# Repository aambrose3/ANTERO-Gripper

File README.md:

ANTERO-Gripper
MATLAB code for modeling, optimizing, and experimentally evaluating the ANTERO gripper and its 5-bar, 3-DOF (5B3D) finger mechanism.
This repository brings together:
a static finger model for contact-force estimation,
finger geometry and compliance optimization studies,
beam spring optimization scripts,
force-control analysis utilities, and
grasp-force validation scripts based on experimental data.
Repository structure
`5B3D-Finger-Model`
Baseline 5B3D finger static model and contact-force estimation code.
Key files:
`Main.m` — runs the main static-model sweep and saves results into the `Results/` directory.
`contactSolver.m`, `fastContactSolver.m`, `getJacobians.m`, `getParam.m`, `getSpring.m`, `updateParam.m` — supporting model functions.
`Results/` — generated outputs and follow-on plotting/analysis scripts.
`5B3D-Finger-Optimization`
Finger design-space exploration and optimization utilities.
Key files:
`Main.m` — runs a model sweep over finger states.
`Optimization.m` — performs design optimization over parameters such as link length and compliance-related terms.
`OptimizationAnalysis.m` — post-processes optimization outputs.
`FingerLinkOptimization.m` — helper script for optimization studies.
`Results/` — saved outputs and visualizations.
`5B3D-Spring-Optimization`
Beam spring modeling and stiffness optimization.
Key files:
`OptimizeSpringStiffness.m` — main entry point for spring optimization.
`solveBVP.m`, `bcfcn.m`, `initFcn.m` — boundary-value-problem setup.
`plotSpring.m`, `plotStress.m`, `plotStiffness.m`, `plotThickness.m` — visualization utilities.
`OptimalSpring.mat`, `OptimalSpring_Plus.mat` — saved optimization outputs.
`Force-Control-Testing`
Utilities for unpacking experimental datasets and analyzing force-control / frequency-response behavior.
Key files:
`unpackTeensy.m`
`unpackRokubi.m`
`interpData.m`
`FrequencyResponseAnalysis.m`
`Grasp-Force-Testing`
Scripts for comparing modeled grasp force against measured force-torque data.
Key files:
`Data/unpackTeensyData.m`
`Data/unpackRokubiData.m`
`interpData.m`
`GraspForceTestingAnalysis.m`
plotting utilities and exported figures
`ANTERO-Mid-Level-Control`
Placeholder folder for mid-level control content.
Requirements
This repository is written in MATLAB.
Depending on the scripts you run, you may need MATLAB functionality for:
symbolic math,
parallel computing, and
constrained optimization.
Several scripts also expect local experimental datasets to be available as `.csv`, `.log`, or `.mat` files in specific folder layouts.
Quick start
1. Clone the repository
```bash
git clone https://github.com/aambrose3/ANTERO-Gripper.git
cd ANTERO-Gripper
```
2. Open the repo in MATLAB
Open MATLAB and set the current folder to the repository root, or add the relevant subfolder to your MATLAB path.
3. Run the model or analysis you need
Static 5B3D finger model
```matlab
cd('5B3D-Finger-Model')
run('Main.m')
```
Finger optimization studies
```matlab
cd('5B3D-Finger-Optimization')
run('Main.m')              % model sweep
run('Optimization.m')      % design optimization
```
Spring optimization
```matlab
cd('5B3D-Spring-Optimization')
run('OptimizeSpringStiffness.m')
```
Grasp-force validation workflow
From `Grasp-Force-Testing`, run the scripts in this order:
```matlab
run('Data/unpackTeensyData.m')
run('Data/unpackRokubiData.m')
run('interpData.m')
run('GraspForceTestingAnalysis.m')
```
Expected workflow
5B3D model and optimization
Use the `5B3D-Finger-Model` and `5B3D-Finger-Optimization` folders when you want to:
sweep the finger through joint configurations,
estimate proximal/distal contact forces,
study feasible workspaces,
evaluate mechanical advantage, or
optimize design variables.
Spring design
Use `5B3D-Spring-Optimization` to generate and evaluate compliant spring designs and saved spring models.
Experimental validation
Use `Force-Control-Testing` and `Grasp-Force-Testing` to:
unpack Teensy and Rokubi datasets,
synchronize or interpolate time series,
analyze frequency response, and
compare modeled versus measured grasp force.
Important notes
Hard-coded paths and filenames
Many scripts use hard-coded relative paths and dataset names. Before running them, you will likely need to update file paths for your local machine and dataset organization.
Examples include paths such as:
`60x75\5_HZ\T1.csv`
`60x75\5_HZ\T1-FT.csv`
`Grasp_Force_Testing_Rokubi\90x90\T1.log`
`Data/Matched_Data_60x45.mat`
Results directories
Some scripts save outputs directly into `Results/` or into `.mat` files in the working directory. Running scripts from the intended folder helps avoid path issues.
Research code
This repository appears to be organized as a research codebase rather than a polished MATLAB package. Expect to inspect the top of each script for:
user settings,
sweep ranges,
optimization bounds,
dataset filenames, and
plotting/export behavior.
Suggested order for new users
If you are exploring the repo for the first time, a good path is:
Start with `5B3D-Finger-Model/Main.m` to understand the base model.
Move to `5B3D-Finger-Optimization/Optimization.m` for design studies.
Use `5B3D-Spring-Optimization/OptimizeSpringStiffness.m` for compliant spring design.
Run the experimental workflows in `Grasp-Force-Testing` and `Force-Control-Testing` once your data files are in place.
License
This project is licensed under the Apache License 2.0. See the `LICENSE` file for details.
Author
Repository author: Alexander B. Ambrose
---
If you use this code in academic work, consider citing the repository and any associated publications from the project.

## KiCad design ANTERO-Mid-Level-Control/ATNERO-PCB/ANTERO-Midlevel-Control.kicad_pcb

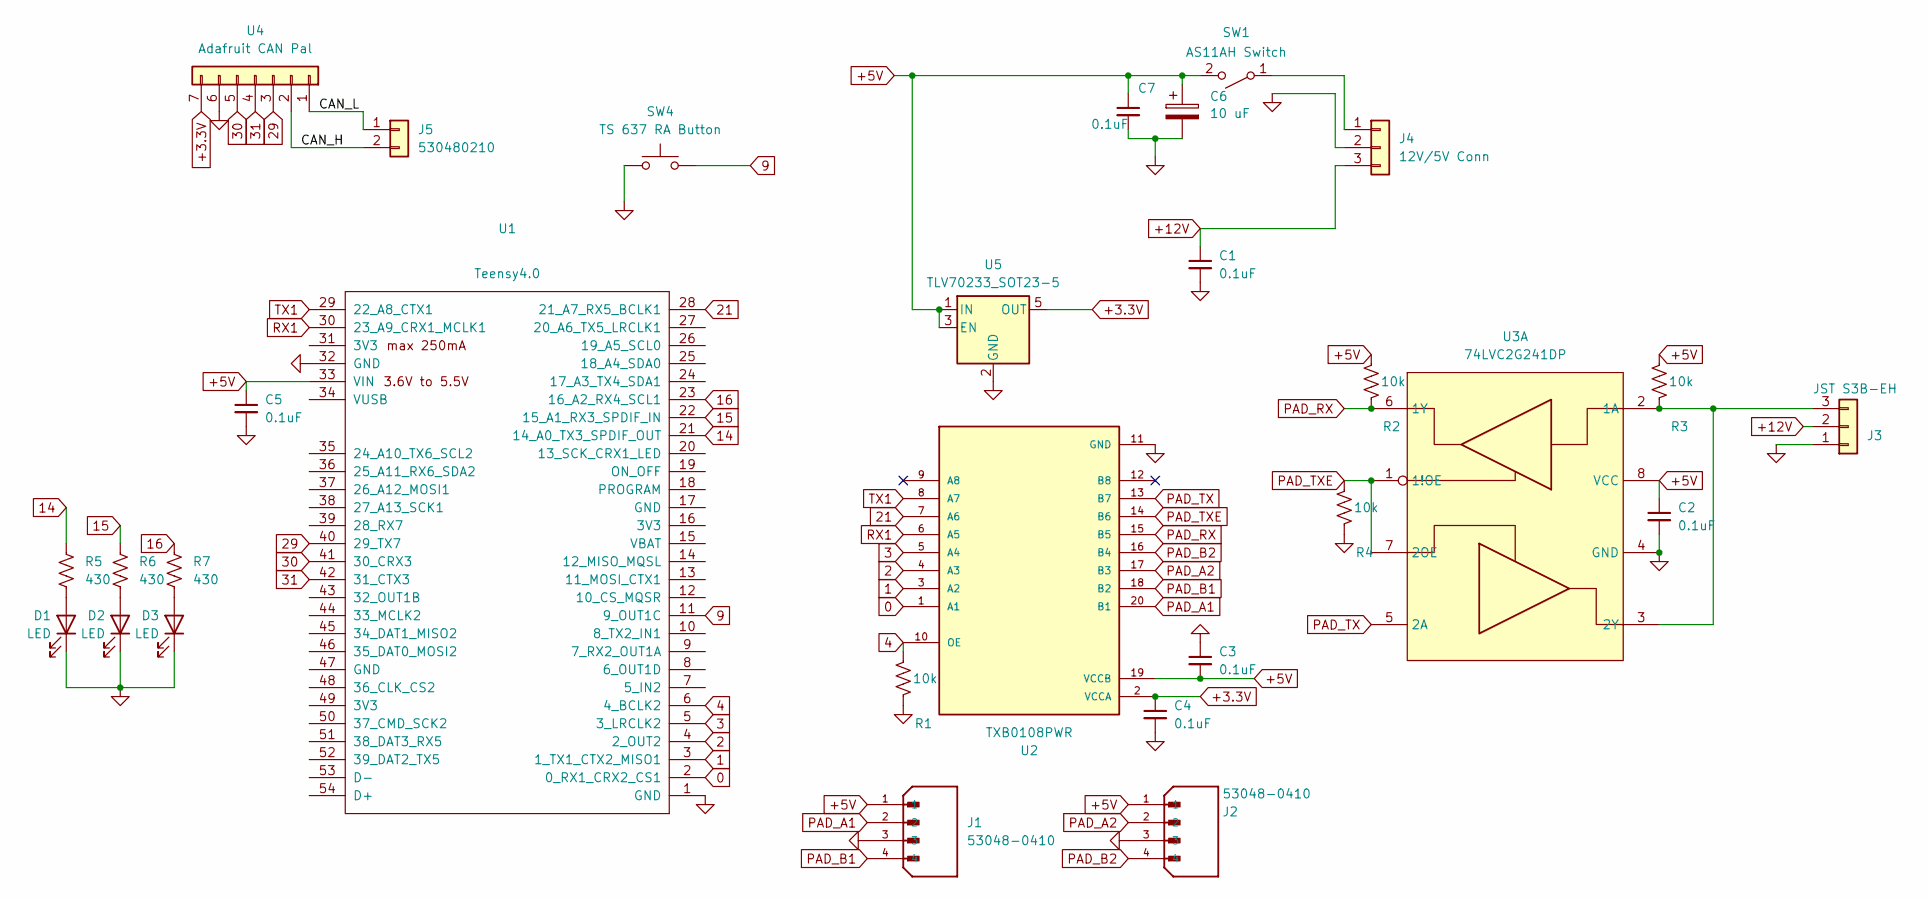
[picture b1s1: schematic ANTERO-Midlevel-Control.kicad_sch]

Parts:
C1, C2, C3, C4, C5, C7: 0.1uF; C_0805_2012Metric_Pad1.18x1.45mm_HandSolder; Digikey N/A
C6: 10 uF; CP_Elec_5x5.8
D1, D2, D3: LED; LED_0402_1005Metric_Pad0.77x0.64mm_HandSolder
J1, J2: 53048-0410; Molex_PicoBlade_53048-0410_1x04_P1.25mm_Horizontal; PARTREV A
J3: JST S3B-EH; JST_EH_S3B-EH_1x03_P2.50mm_Horizontal
J4: 12V/5V Conn; Molex_PicoBlade_53048-0310_1x03_P1.25mm_Horizontal
J5: 530480210; Molex_PicoBlade_53048-0210_1x02_P1.25mm_Horizontal
R1, R2, R3, R4: 10k; R_0805_2012Metric; Digikey N/A
R5, R6, R7: 430; R_0805_2012Metric; Digikey N/A
SW1: AS11AH Switch; AS1XAH
SW4: TS 637 RA Button; TS-637-RA
U1: Teensy4.0; Teensy40_SMT
U2: TXB0108PWR; SOP65P640X120-20N; PARTREV H
U3: 74LVC2G241DP; TSSOP-8_3x3mm_P0.65mm
U4: Adafruit CAN Pal; Adafruit Can Pal; Digikey N/A
U5: TLV70233_SOT23-5; SOT-23-5

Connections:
0: U1.2 (0_RX1_CRX2_CS1), U2.1 (A1)
1: U1.3 (1_TX1_CTX2_MISO1), U2.3 (A2)
2: U1.4 (2_OUT2), U2.4 (A3)
3: U1.5 (3_LRCLK2), U2.5 (A4)
4: R1.2, U1.6 (4_BCLK2), U2.10 (OE)
9: SW4.2, U1.11 (9_OUT1C)
14: R5.2, U1.21 (14_A0_TX3_SPDIF_OUT)
15: R6.2, U1.22 (15_A1_RX3_SPDIF_IN)
16: R7.2, U1.23 (16_A2_RX4_SCL1)
21: U1.28 (21_A7_RX5_BCLK1), U2.7 (A6)
29: U1.40 (29_TX7), U4.3 (RX)
30: U1.41 (30_CRX3), U4.5 (SLNT)
31: U1.42 (31_CTX3), U4.4 (TX)
+3.3V: C4.1, U2.2 (VCCA), U4.7 (CANL), U5.5 (OUT)
+5V: C2.1, C3.2, C5.1, C6.1, C7.1, J1.1, J2.1, R2.2, R3.2, SW1.2 (B), U1.33 (VIN), U2.19 (VCCB), U3.8 (VCC), U5.1 (IN), U5.3 (EN)
+12V: C1.1, J3.2, J4.3
/CAN_H: J5.2, U4.2 (GND)
/CAN_L: J5.1, U4.1 (Vcc)
GND: C1.2, C2.2, C3.1, C4.2, C5.2, C6.2, C7.2, D1.1 (K), D2.1 (K), D3.1 (K), J1.3, J2.3, J3.1, J4.2, R1.1, R4.1, SW4.1, U1.1 (GND), U1.32 (GND), U2.11 (GND), U3.4 (GND), U4.6 (CANH), U5.2 (GND)
unnamed: D1.2 (A), R5.1
unnamed: D2.2 (A), R6.1
unnamed: D3.2 (A), R7.1
unnamed: J3.3, R3.1, U3.2 (1A), U3.3 (2Y)
unnamed: J4.1, SW1.1 (A)
PAD_A1: J1.2, U2.20 (B1)
PAD_A2: J2.2, U2.17 (B3)
PAD_B1: J1.4, U2.18 (B2)
PAD_B2: J2.4, U2.16 (B4)
PAD_RX: R2.1, U2.15 (B5), U3.6 (1Y)
PAD_TX: U2.13 (B7), U3.5 (2A)
PAD_TXE: R4.2, U2.14 (B6), U3.1 (1!OE), U3.7 (2OE)
RX1: U1.30 (23_A9_CRX1_MCLK1), U2.6 (A5)
TX1: U1.29 (22_A8_CTX1), U2.8 (A7)

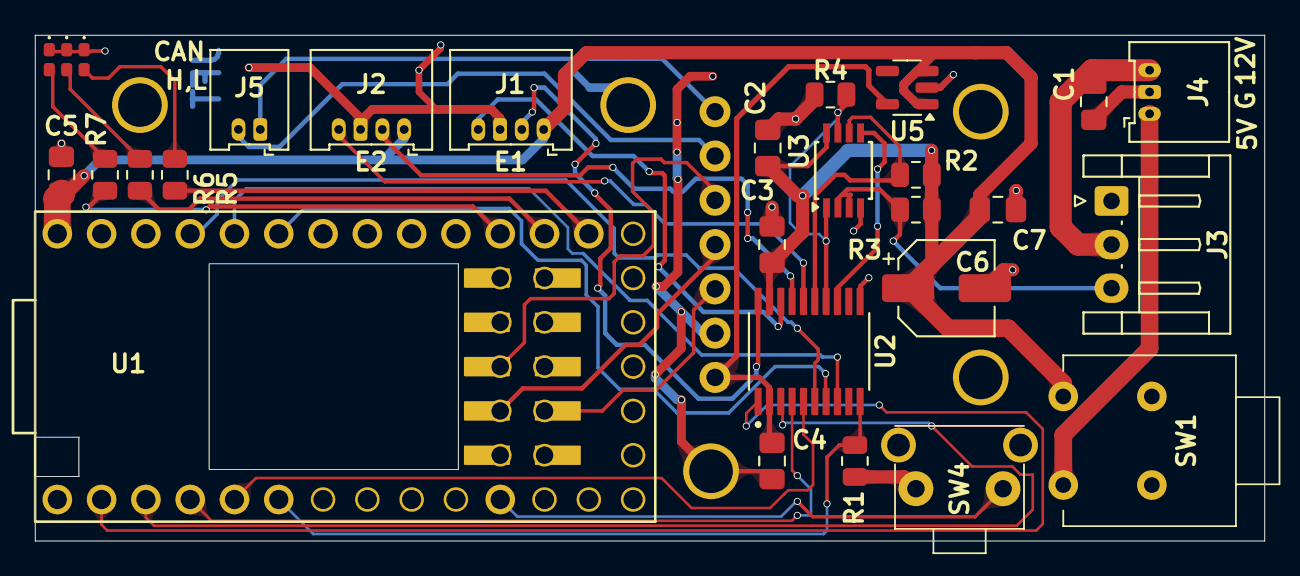
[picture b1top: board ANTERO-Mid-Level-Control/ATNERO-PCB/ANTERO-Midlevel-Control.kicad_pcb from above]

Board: 2 copper layers, 70.5 x 29.0 mm, 29 parts (1 on the bottom side), 33 nets.

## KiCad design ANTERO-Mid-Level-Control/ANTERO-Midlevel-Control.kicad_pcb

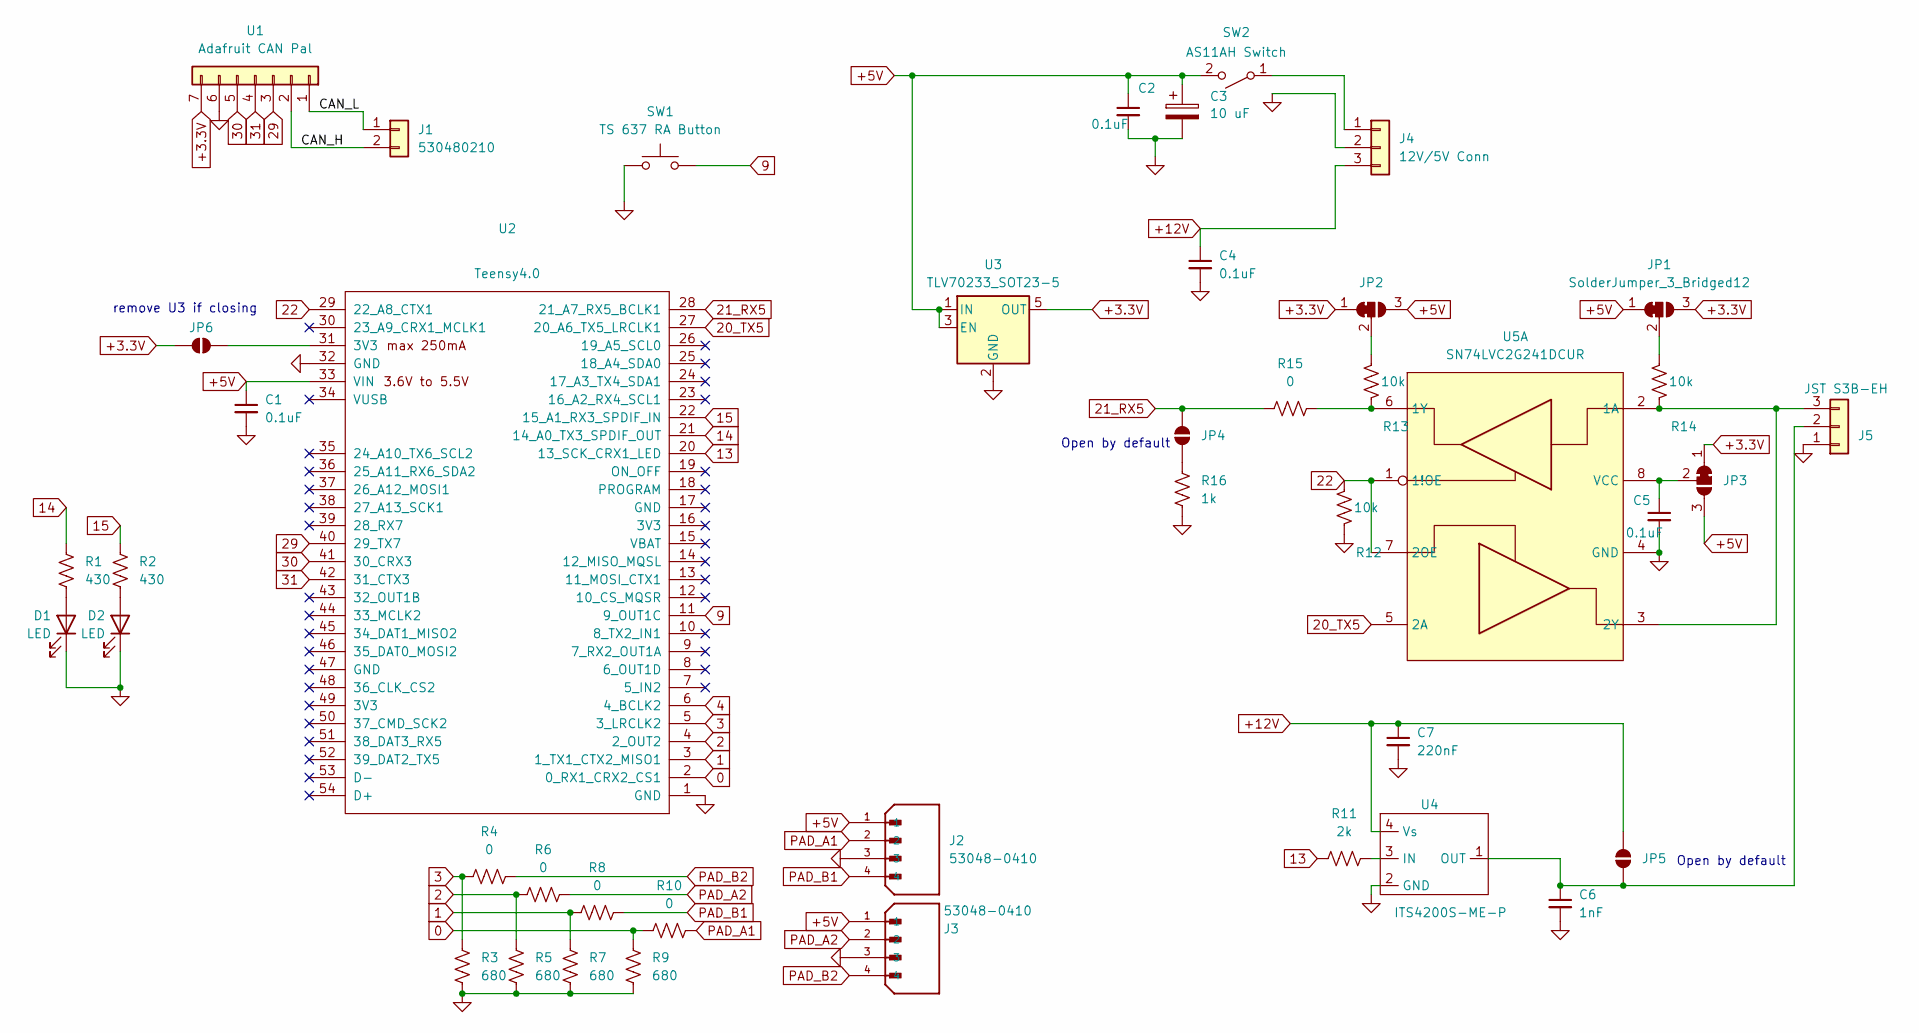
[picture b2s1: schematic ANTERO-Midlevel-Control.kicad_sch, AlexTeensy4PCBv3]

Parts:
C1, C2, C4, C5: 0.1uF; C_0805_2012Metric_Pad1.18x1.45mm_HandSolder; Digikey N/A
C3: 10 uF; CP_Elec_5x5.8
C6: 1nF; C_0805_2012Metric_Pad1.18x1.45mm_HandSolder; Digikey N/A
C7: 220nF; C_0805_2012Metric_Pad1.18x1.45mm_HandSolder; Digikey N/A
D1, D2: LED; LED_0402_1005Metric_Pad0.77x0.64mm_HandSolder
J1: 530480210; Molex_PicoBlade_53048-0210_1x02_P1.25mm_Horizontal
J2, J3: 53048-0410; Molex_PicoBlade_53048-0410_1x04_P1.25mm_Horizontal; PARTREV A
J4: 12V/5V Conn; Molex_PicoBlade_53048-0310_1x03_P1.25mm_Horizontal
J5: JST S3B-EH; JST_EH_S3B-EH_1x03_P2.50mm_Horizontal
JP1, JP2, JP3: SolderJumper_3_Bridged12; SolderJumper-3_P1.3mm_Bridged12_RoundedPad1.0x1.5mm_NumberL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
JP4: SolderJumper_2_Open; SolderJumper-2_P1.3mm_Open_Pad1.0x1.5mm_SMALLER
JP5, JP6: SolderJumper_2_Open; SolderJumper-2_P1.3mm_Open_RoundedPad1.0x1.5mm
R1, R2: 430; R_0805_2012Metric; Digikey N/A
R3, R5, R7, R9: 680; R_0805_2012Metric; Digikey N/A
R4, R6, R8, R10, R15: 0; R_0805_2012Metric; Digikey N/A
R11: 2k; R_0805_2012Metric; Digikey N/A
R12, R13, R14: 10k; R_0805_2012Metric; Digikey N/A
R16: 1k; R_0805_2012Metric; Digikey N/A
SW1: TS 637 RA Button; TS-637-RA
SW2: AS11AH Switch; AS1XAH
U1: Adafruit CAN Pal; Adafruit Can Pal; Digikey N/A
U2: Teensy4.0; Teensy40_SMT
U3: TLV70233_SOT23-5; SOT-23-5
U4: ITS4200S-ME-P; SOT-223
U5: SN74LVC2G241DCUR; VSSOP-8_2.3x2mm_P0.5mm

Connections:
0: R9.2, R10.1, U2.2 (0_RX1_CRX2_CS1)
1: R7.2, R8.1, U2.3 (1_TX1_CTX2_MISO1)
2: R5.2, R6.1, U2.4 (2_OUT2)
3: R3.2, R4.1, U2.5 (3_LRCLK2)
4: U2.6 (4_BCLK2)
9: SW1.2, U2.11 (9_OUT1C)
13: R11.1, U2.20 (13_SCK_CRX1_LED)
14: R1.2, U2.21 (14_A0_TX3_SPDIF_OUT)
15: R2.2, U2.22 (15_A1_RX3_SPDIF_IN)
20_TX5: U2.27 (20_A6_TX5_LRCLK1), U5.5 (2A)
21_RX5: JP4.2 (B), R15.1, U2.28 (21_A7_RX5_BCLK1)
22: R12.2, U2.29 (22_A8_CTX1), U5.1 (1!OE), U5.7 (2OE)
29: U1.3 (RX), U2.40 (29_TX7)
30: U1.5 (SLNT), U2.41 (30_CRX3)
31: U1.4 (TX), U2.42 (31_CTX3)
+3.3V: JP1.3 (B), JP2.1 (A), JP3.1 (A), JP6.2 (B), U1.7 (CANL), U3.5 (OUT)
+5V: C1.1, C2.1, C3.1, J2.1, J3.1, JP1.1 (A), JP2.3 (B), JP3.3 (B), SW2.2 (B), U2.33 (VIN), U3.1 (IN), U3.3 (EN)
+12V: C4.1, C7.1, J4.3, JP5.2 (B), U4.4 (Vs)
/CAN_H: J1.2, U1.2 (GND)
/CAN_L: J1.1, U1.1 (Vcc)
GND: C1.2, C2.2, C3.2, C4.2, C5.2, C6.2, C7.2, D1.1 (K), D2.1 (K), J2.3, J3.3, J4.2, J5.1, R3.1, R5.1, R7.1, R9.1, R12.1, R16.1, SW1.1, U1.6 (CANH), U2.1 (GND), U2.32 (GND), U3.2 (GND), U4.2 (GND), U5.4 (GND)
unnamed: D1.2 (A), R1.1
unnamed: D2.2 (A), R2.1
unnamed: J4.1, SW2.1 (A)
unnamed: C6.1, J5.2, JP5.1 (A), U4.1 (OUT)
unnamed: J5.3, R14.1, U5.2 (1A), U5.3 (2Y)
unnamed: JP1.2 (C), R14.2
unnamed: JP2.2 (C), R13.2
unnamed: C5.1, JP3.2 (C), U5.8 (VCC)
unnamed: JP4.1 (A), R16.2
unnamed: JP6.1 (A), U2.31 (3V3)
unnamed: R11.2, U4.3 (IN)
unnamed: R13.1, R15.2, U5.6 (1Y)
PAD_A1: J2.2, R10.2
PAD_A2: J3.2, R6.2
PAD_B1: J2.4, R8.2
PAD_B2: J3.4, R4.2

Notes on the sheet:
Open by default
remove U3 if closing

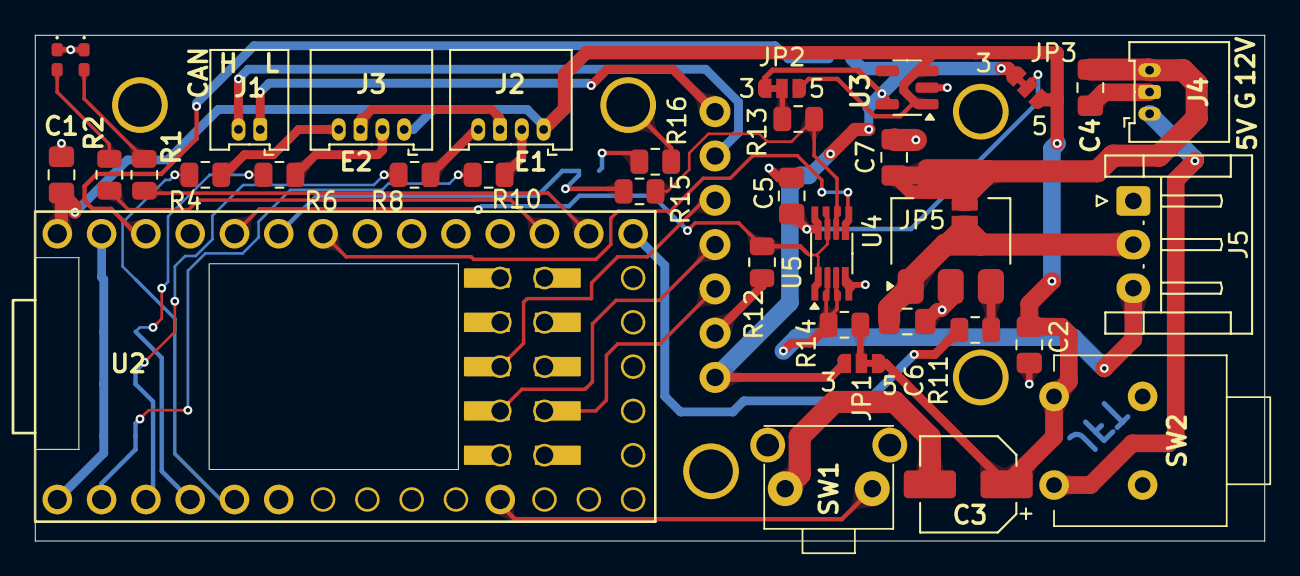
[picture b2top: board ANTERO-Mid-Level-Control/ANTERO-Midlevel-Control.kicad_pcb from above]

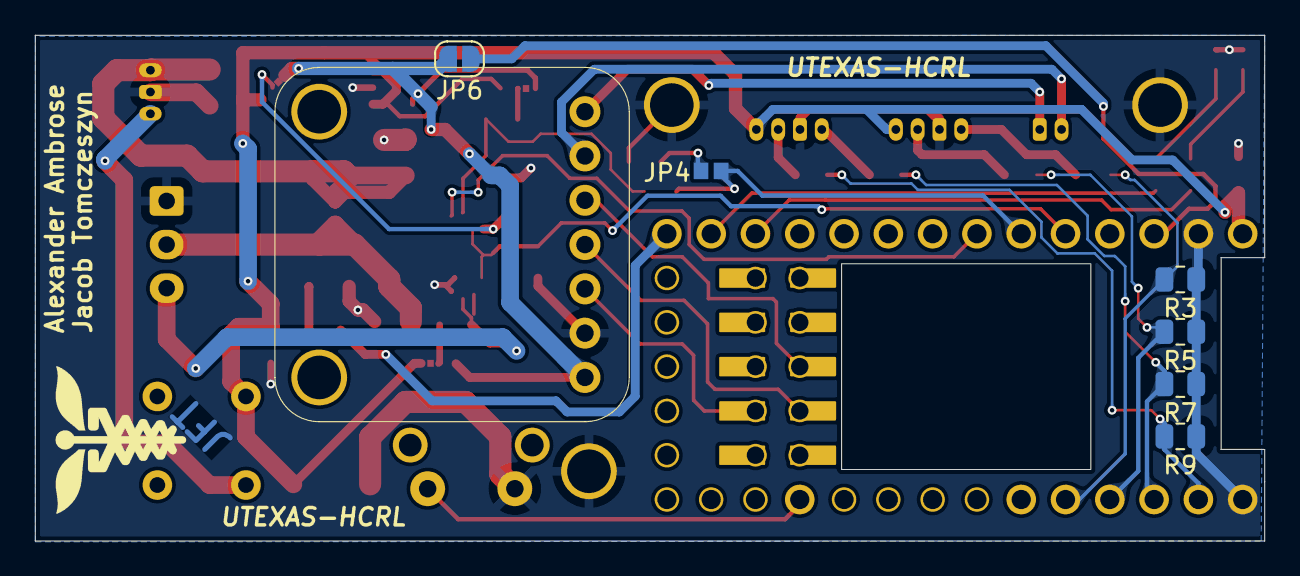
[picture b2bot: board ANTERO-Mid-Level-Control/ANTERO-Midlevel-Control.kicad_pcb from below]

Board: 2 copper layers, 70.5 x 29.0 mm, 43 parts (7 on the bottom side), 36 nets.

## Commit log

2026-04-14 Reinit
2026-04-14 Init
2026-04-14 Uploading the PCB Files
2026-05-11 Cleaned up repository and restructured the repository.
